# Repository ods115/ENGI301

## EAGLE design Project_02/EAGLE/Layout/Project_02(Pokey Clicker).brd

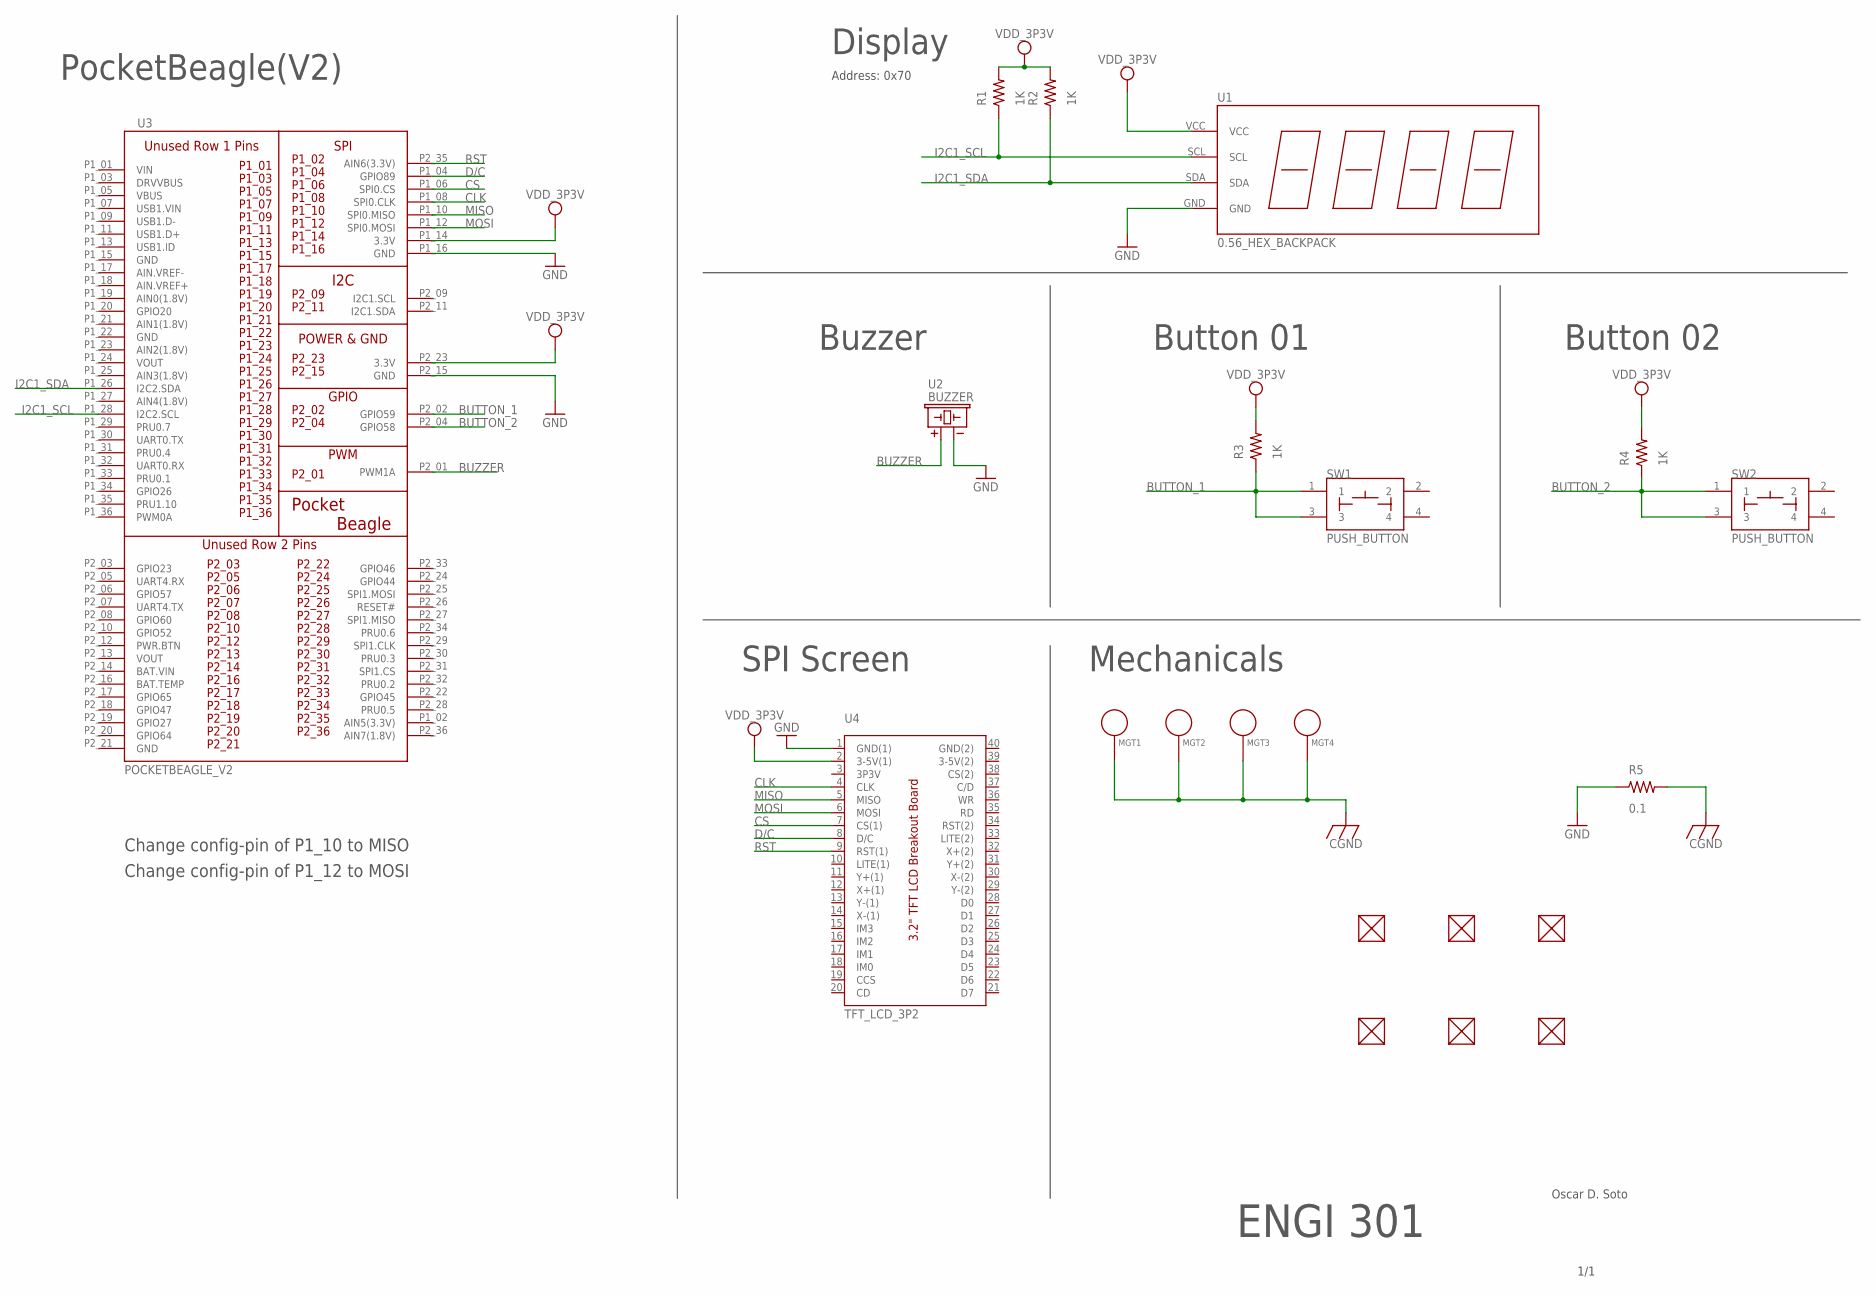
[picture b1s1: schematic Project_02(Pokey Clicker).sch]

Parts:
FUD1, FUD2, FUD3, FUD4, FUD5, FUD6: FIDUCIAL; FIDUCIAL_40MIL
MGT1, MGT2, MGT3, MGT4: MOUNTING_HOLE
R1, R2, R3, R4: 1K; R0603
R5: 0.1; R1206
SW1, SW2: PUSH_BUTTON; BUTTON_12.5MM
U1: 0.56_HEX_BACKPACK
U2: BUZZER; BUZZER_6.5MM
U3: POCKETBEAGLE_V2; POCKETBEAGLE
U4: TFT_LCD_3P2

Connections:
BAT.VIN: U3.P2_14 (BAT.VIN)
BUTTON_1: R3.1, SW1.1, SW1.3, U3.P2_02 (GPIO59)
BUTTON_2: R4.1, SW2.1, SW2.3, U3.P2_04 (GPIO58)
BUZZER: U2.+, U3.P2_01 (PWM1A)
CGND: MGT1.P$1, MGT2.P$1, MGT3.P$1, MGT4.P$1, R5.2
CLK: U3.P1_08 (SPI0.CLK), U4.4 (CLK)
CS: U3.P1_06 (SPI0.CS), U4.7 (CS(1))
D/C: U3.P1_04 (GPIO89), U4.8 (D/C)
GND: R5.1, U1.GND, U2.-, U3.P1_16 (GND), U3.P1_22 (GND), U3.P2_15 (GND), U3.P2_21 (GND), U4.1 (GND(1))
I2C1_SCL: R1.1, U1.SCL, U3.P1_28 (I2C2.SCL)
I2C1_SDA: R2.1, U1.SDA, U3.P1_26 (I2C2.SDA)
MISO: U3.P1_10 (SPI0.MISO), U4.5 (MISO)
MOSI: U3.P1_12 (SPI0.MOSI), U4.6 (MOSI)
RST: U3.P2_35 (AIN6(3.3V)), U4.9 (RST(1))
VDD_3P3V: R1.2, R2.2, R3.2, R4.2, U1.VCC, U3.P1_14 (3.3V), U3.P2_23 (3.3V), U4.2 (3-5V(1))
VIN: U3.P1_01 (VIN)
VOUT: U3.P1_24 (VOUT), U3.P2_13 (VOUT)

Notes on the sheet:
PocketBeagle(V2)
Address: 0x70
Buzzer
SPI Screen
Button 02
Button 01
Display
Mechanicals
Change config-pin of P1_12 to MOSI
Change config-pin of P1_10 to MISO
ENGI 301
Oscar D. Soto
1/1

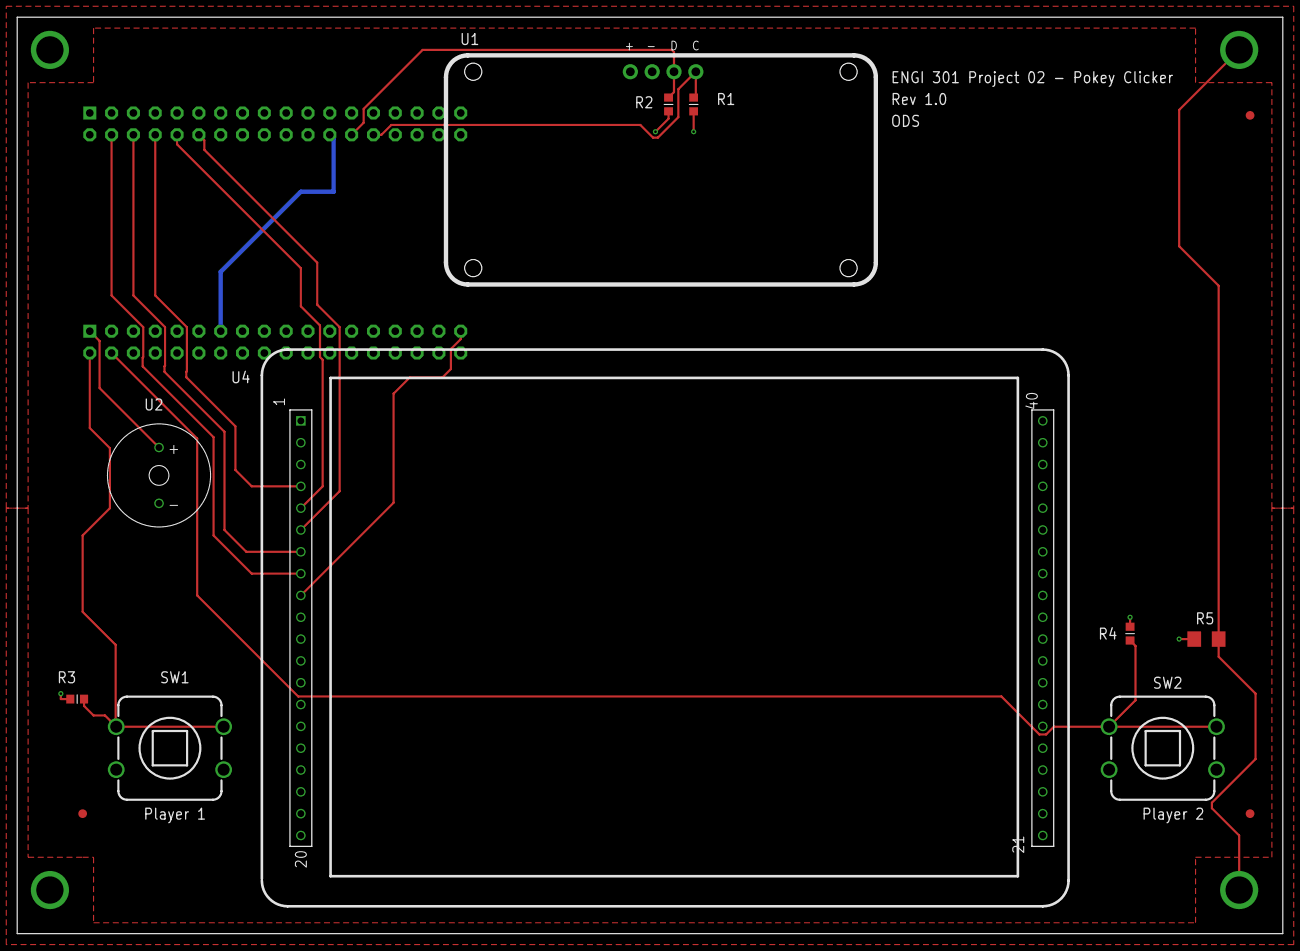
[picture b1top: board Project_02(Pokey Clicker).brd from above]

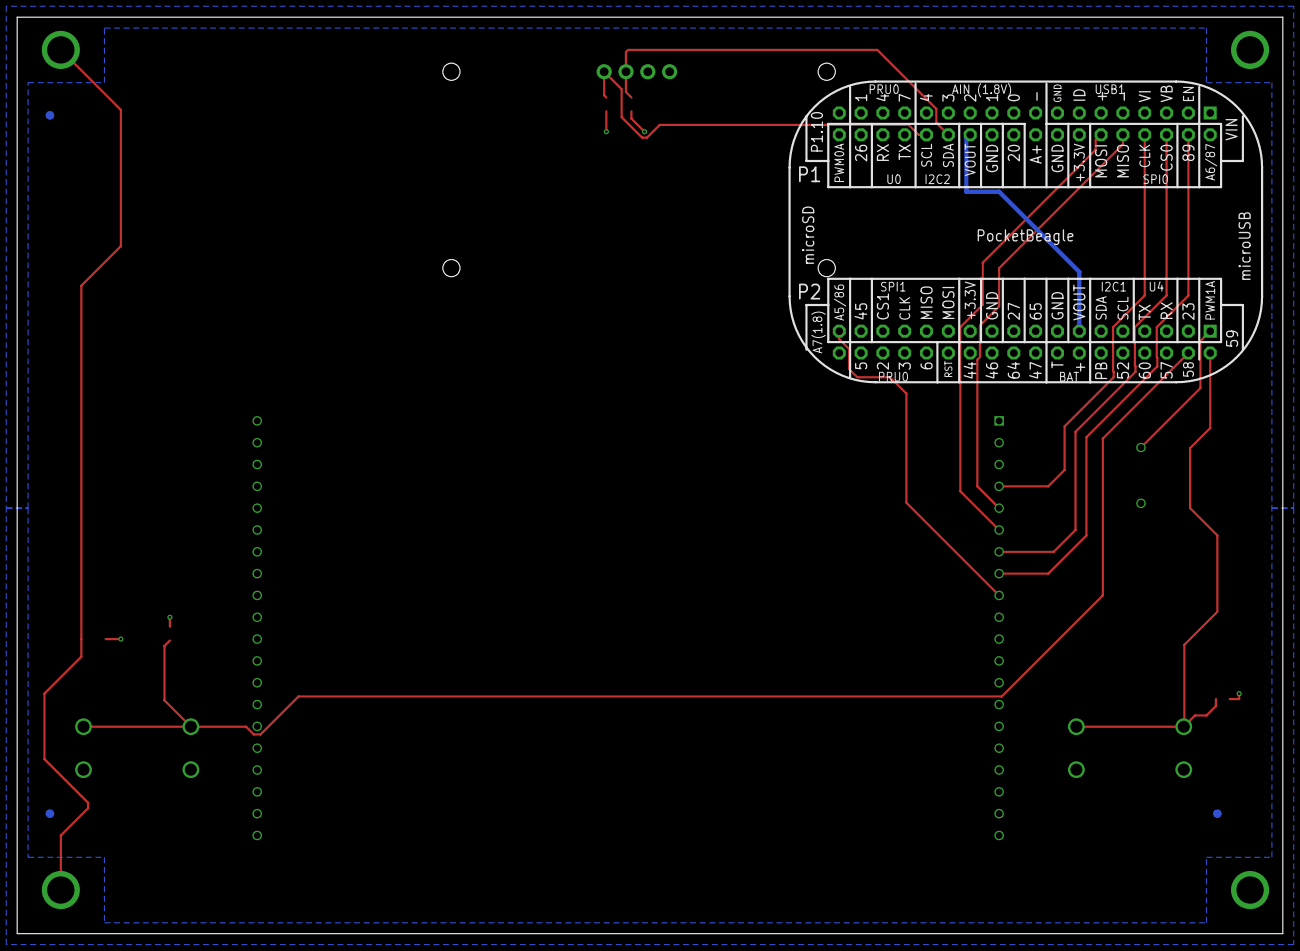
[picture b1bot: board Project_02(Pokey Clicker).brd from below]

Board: 4 copper layers, 147.3 x 106.7 mm, 21 parts (5 on the bottom side), 15 nets.

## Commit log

2021-09-25 Create a temp.txt for class
2021-10-02 Create simple_calc
2021-10-02 Update simple_calc
2021-10-12 Adding simple_calc function to Git
2021-10-20 Create project_01
2021-10-20 Create soto_ENGI301_projectproposal
2021-10-20 Adding a blinking LED function to python
2021-11-07 Create Main_game.py
    This is the script which runs the main game. It compiles everything from the button operation to the screen setup. All functions have been localized to this one piece of code to make implementation s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
2021-11-07 Create run
    This is a run script for the Main_game.py code. This script gets run on bootup by the sudo crontab to make the game begin on startup.
2021-11-18 Create docs
2021-11-18 Create Project_02_proposal
2021-11-18 Create p
2021-11-18 Create oo
2021-11-26 Create po
2021-11-26 Create Project_02_schematic
2021-11-26 Create layout_project02
2021-11-26 Create library_project02
2021-11-26 Rename Project_02_schematic to Project_02
2021-11-26 Rename library_project02 to Project02
2021-11-26 Rename Project02 to Project_02
2021-11-26 Rename layout_project02 to Project_02
2021-12-14 Create Project_02
